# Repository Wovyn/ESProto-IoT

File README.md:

# ESProto-IoT

The ESProto IoT is an ESP8266 prototyping PCB made for the AI Thinker ESP-12F modules, and designed to support IoT ("Internet of Things") sensors and peripherals from SeeedStudio/Grove, DFRobot, and ControlEverything.

## How does it work?

The ESP8266 is more powerful than the Arduino Pro Mini--so why not use it as the "main" microcontroller, and drive the Arduino Pro Mini as a peripheral? We do that by communicating with the Arduino Pro Mini over I2C ("I-squared-C"). The advantage to this arrangement is a board that can speak to all of the 5V sensors and actuators that already work with your Arduino, with the added speed and WiFi capability of the ESP8266.

## Design Images

## PDFs

[View PDFs](Docs/PDF)

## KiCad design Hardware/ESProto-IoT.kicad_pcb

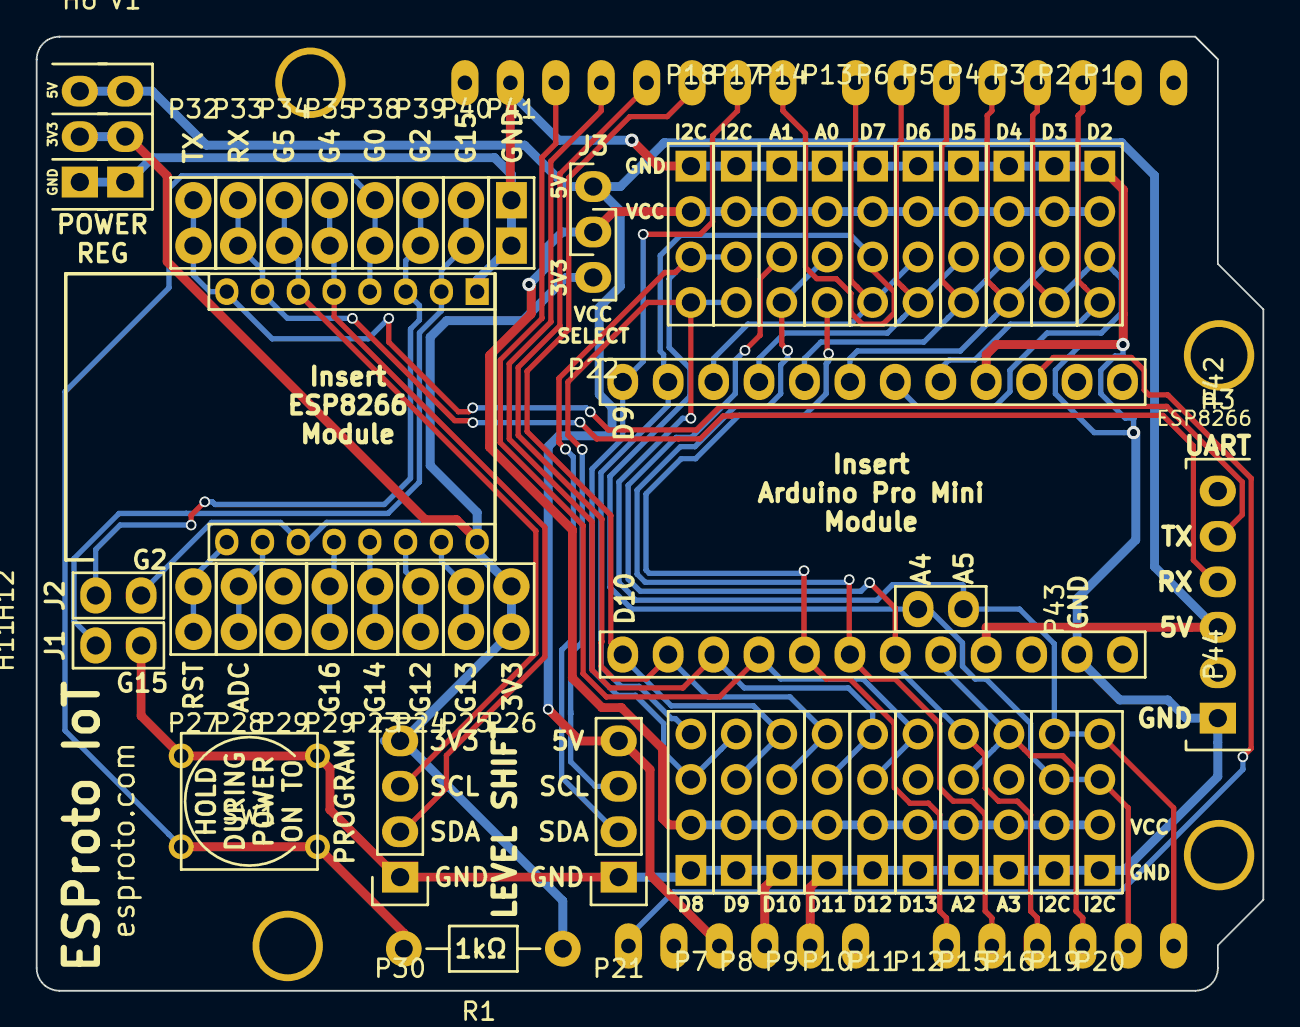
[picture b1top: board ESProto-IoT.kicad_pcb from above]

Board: 2 copper layers, 68.6 x 53.3 mm, 52 parts (0 on the bottom side), 36 nets.

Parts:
H3: UART; Pin_Header_Straight_1x06
H5: L0; Pin_Header_Straight_1x08_Pitch2.00mm
H6: VRegOut; Pin_Header_Straight_1x03
H7: R0; Pin_Header_Straight_1x08_Pitch2.00mm
H11: GPIO15_GND; Pin_Header_Straight_1x02
H12: GPIO2_VCC; Pin_Header_Straight_1x02
IC1: ARDUINO_PRO_MINI_5V; ARDUINO_SHIELD
P1: DIGITAL_02; Pin_Header_Straight_1x04_C
P2: DIGITAL_03; Pin_Header_Straight_1x04_C
P3: DIGITAL_04; Pin_Header_Straight_1x04_C
P4: DIGITAL_05; Pin_Header_Straight_1x04_C
P5: DIGITAL_06; Pin_Header_Straight_1x04_C
P6: DIGITAL_07; Pin_Header_Straight_1x04_C
P7: DIGITAL_08; Pin_Header_Straight_1x04_C
P8: DIGITAL_09; Pin_Header_Straight_1x04_C
P9: DIGITAL_10; Pin_Header_Straight_1x04_C
P10: DIGITAL_11; Pin_Header_Straight_1x04_C
P11: DIGITAL_12; Pin_Header_Straight_1x04_C
P12: DIGITAL_13X; Pin_Header_Straight_1x04_C
P13: ANALOG_00; Pin_Header_Straight_1x04_C
P14: ANALOG_01; Pin_Header_Straight_1x04_C
P15: ANALOG_02; Pin_Header_Straight_1x04_C
P16: ANALOG_03X; Pin_Header_Straight_1x04_C
P17: I2C_01; Pin_Header_Straight_1x04_C
P18: I2C_02; Pin_Header_Straight_1x04_C
P19: I2C_03; Pin_Header_Straight_1x04_C
P20: I2C_04; Pin_Header_Straight_1x04_C
P21: LEVEL_A; Pin_Header_Straight_1x04
P22: POWER_A; Pin_Header_Straight_1x03
P23: ESP_G14; Pin_Header_Straight_1x02
P24: ESP_G12; Pin_Header_Straight_1x02
P25: ESP_G13; Pin_Header_Straight_1x02
P26: ESP_3V3; Pin_Header_Straight_1x02
P27: ESP_RST; Pin_Header_Straight_1x02
P28: ESP_ADC; Pin_Header_Straight_1x02
P29, P29#2: ESP_G16; Pin_Header_Straight_1x02
P30: LEVEL_B; Pin_Header_Straight_1x04
P32: ESP_TX; Pin_Header_Straight_1x02
P33: ESP_RX; Pin_Header_Straight_1x02
P34: ESP_G5; Pin_Header_Straight_1x02
P35: ESP_G4; Pin_Header_Straight_1x02
P38: ESP_G0; Pin_Header_Straight_1x02
P39: ESP_G2; Pin_Header_Straight_1x02
P40: ESP_G15; Pin_Header_Straight_1x02
P41: ESP_GND; Pin_Header_Straight_1x02
P42: ARDUINO_L; Pin_Header_Straight_1x12
P43: I2C_A4_A5; Pin_Header_Straight_1x02
P44: ARDUINO_R; Pin_Header_Straight_1x12
R1: 1kΩ; Resistor_Horizontal_RM10mm
SW1: PROGRAM; SW_PUSH_SMALL
V1: Voltage_Regulator; Pin_Header_Straight_1x03

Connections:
+3V3: H5.3, H5.8, H6.2, H12.2, P22.1, P26.1, P26.2, P30.4, R1.1, V1.2
+5V: H3.4, H6.1, IC1.5V, P21.4, P22.3, P44.4, V1.1
A0: IC1.AD0, P13.4, P44.8
A1: IC1.AD1, P13.3, P14.4, P44.7
A2: IC1.AD2, P14.3, P15.4, P44.6
A3: IC1.AD3, P15.3, P16.4, P44.5
ADC: H5.2, P28.1, P28.2
D2: IC1.2, P1.4, P42.5
D3: IC1.3, P1.3, P2.4, P42.6
D4: IC1.4, P2.3, P3.4, P42.7
D5: IC1.5, P3.3, P4.4, P42.8
D6: IC1.6, P4.3, P5.4, P42.9
D7: IC1.7, P5.3, P6.4, P42.10
D8: IC1.8, P6.3, P7.4, P42.11
D9: IC1.9, P7.3, P8.4, P42.12
D10: IC1.10, P8.3, P9.4, P44.12
D11: IC1.11, P9.3, P10.4, P44.11
D12: IC1.12, P10.3, P11.4, P44.10
D13: IC1.13, P11.3, P12.4, P44.9
GND: H3.6, H6.3, H7.8, H11.2, IC1.GND1, IC1.GND2, IC1.GND3, P1.1, P2.1, P3.1, P4.1, P5.1, P6.1, P7.1, P8.1, P9.1, P10.1, P11.1, P12.1, P13.1, P14.1, P15.1, P16.1, P17.1, P18.1, P19.1, P20.1, P21.1, P30.1, P41.1, P41.2, P42.4, P44.2, SW1.2, V1.3
GPIO0: H7.5, P38.1, P38.2, R1.2, SW1.1
GPIO2: H7.6, H12.1, P39.1, P39.2
GPIO12: H5.6, P24.1, P24.2
GPIO13: H5.7, P25.1, P25.2
GPIO14: H5.5, P23.1, P23.2
GPIO15: H7.7, H11.1, P40.1, P40.2
GPIO16: H5.4, P29#2.1, P29#2.2
unnamed: P1.2, P2.2, P3.2, P4.2, P5.2, P6.2, P7.2, P8.2, P9.2, P10.2, P11.2, P12.2, P13.2, P14.2, P15.2, P16.2, P17.2, P18.2, P19.2, P20.2, P22.2
REST: H5.1, P27.1, P27.2
RST2: IC1.RST, P42.3
RXD1: H3.3, H7.2, P33.1, P33.2
SCL: IC1.AD5, P17.4, P18.4, P19.4, P20.4, P21.3, P43.1
SCL_ESP: H7.3, P30.3, P34.1, P34.2
SDA: IC1.AD4, P17.3, P18.3, P19.3, P20.3, P21.2, P43.2
SDA_ESP: H7.4, P30.2, P35.1, P35.2
TXD1: H3.2, H7.1, P32.1, P32.2

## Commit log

2016-02-09 Create LICENSE
2016-02-09 Add KiCad schema, pcb files
2016-02-09 Add images
2016-02-09 Fix images
2016-03-13 Update to v20160308
2016-03-15 Updated IoT
2016-03-15 Updated images of IoT. Updated Readme.
2016-03-15 Update gitignore
2016-04-21 Update to add more space, better labels
2016-04-26 Latest PCB
